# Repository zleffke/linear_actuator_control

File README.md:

# linear_actuator_control
KiCAD layout &amp; Arduino code for large linear actuator controller

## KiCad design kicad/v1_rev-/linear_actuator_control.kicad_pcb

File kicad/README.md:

# linear_actuator_control
KiCAD layout for linear actuator controller

### Directories:

v1_rev- : Initial KiCAD design

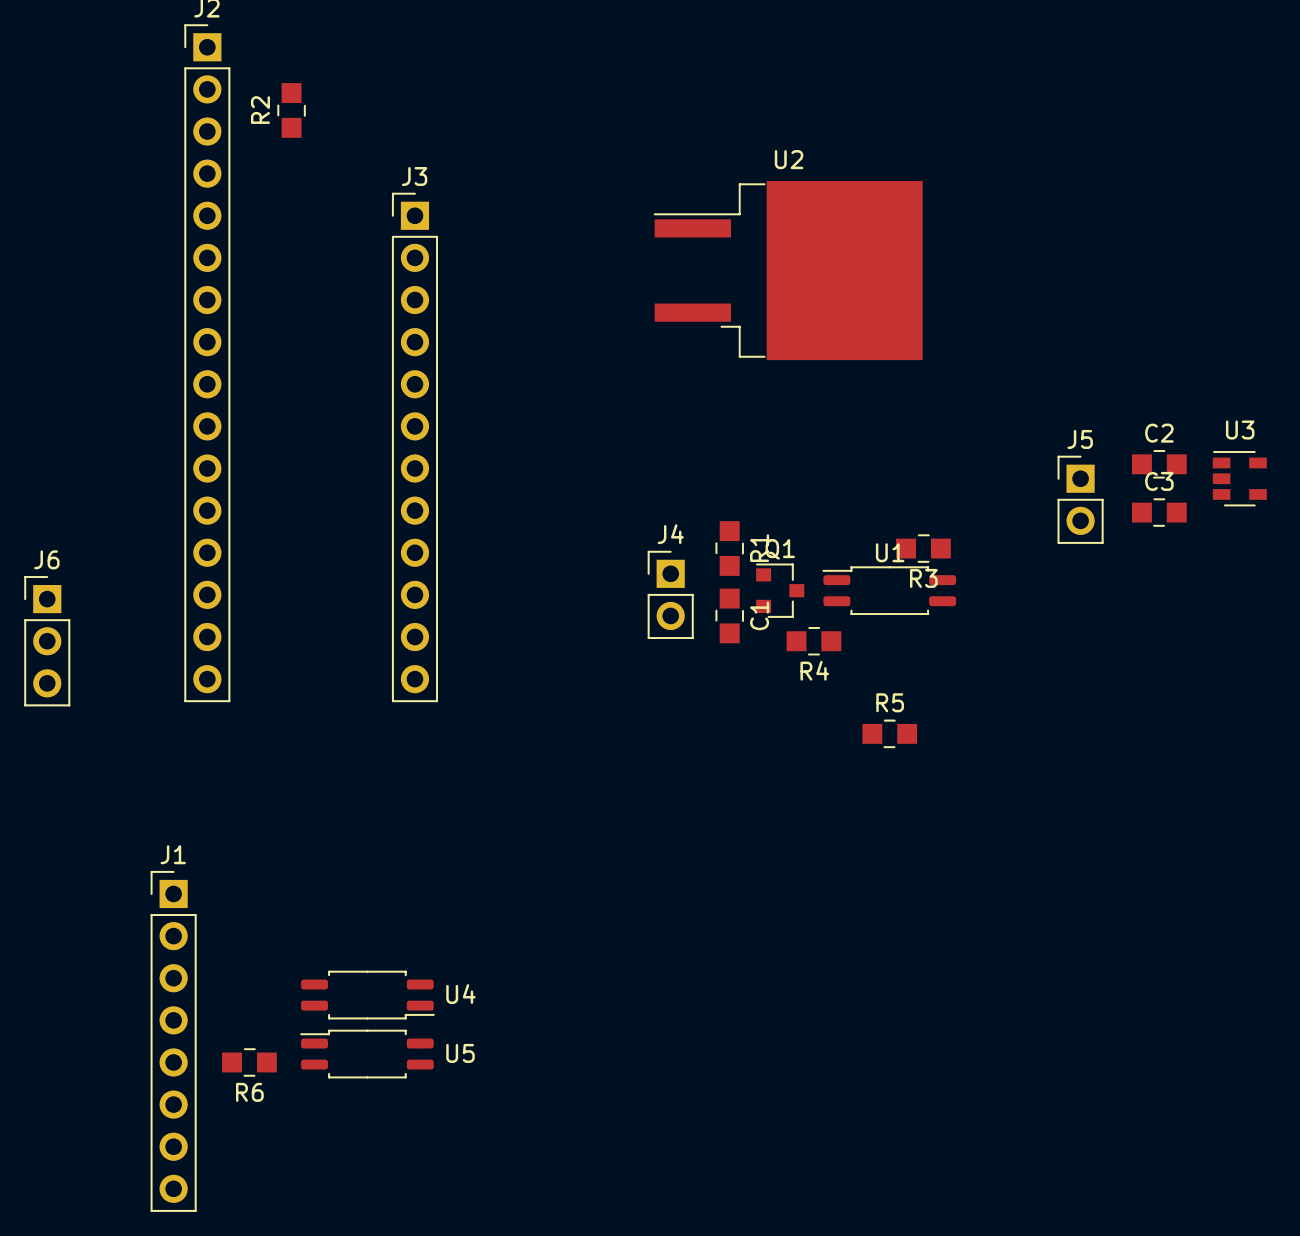
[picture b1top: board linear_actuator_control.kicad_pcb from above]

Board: 2 copper layers, 21 parts (0 on the bottom side), 18 nets, no tracks yet.

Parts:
C1, C2, C3: C; 0805
J1: G2_24v13; PinHeader_1x08_P2.54mm_Vertical
J2: feather32u4; PinHeader_1x16_P2.54mm_Vertical
J3: feather32u4; PinHeader_1x12_P2.54mm_Vertical
J4: Sensor; PinHeader_1x02_P2.54mm_Vertical
J5: Power; PinHeader_1x02_P2.54mm_Vertical
J6: LCD; PinHeader_1x03_P2.54mm_Vertical
Q1: DMG3414U; SOT-23
R1, R2, R3: 10k; 0805
R4, R5: 1k; 0805
R6: 270; 0805
U1, U4, U5: FODM217C; SOP-4_4.4x2.6mm_P1.27mm
U2: NCV8674; TO-263-2
U3: SPX3819M5-L-5-0; SOT-23-5

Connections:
0_RX: J2.14, R3.1, U1.4
1_TX: J2.15, J6.2
5_PWM: J1.3, J3.10
6: J1.2, J3.9
18_A0: J1.6, J2.5
19_A1: J2.6, R5.1
+3V3: J2.2, R2.2, R3.2, U5.1
+12V: C3.1, R1.1, U1.1, U2.3
GND: C1.2, C2.2, C3.2, J1.1, J2.4, J2.16, J4.2, J5.2, J6.3, Q1.2, U1.3, U2.2, U4.2, U4.3, U5.3
unnamed: C1.1, J4.1, Q1.1, R1.2
unnamed: C2.1, J5.1, U2.1
unnamed: Q1.3, R4.2
unnamed: R4.1, U1.2
unnamed: R5.2, U4.1
unnamed: R6.1, U5.2
SCL: J3.11, R2.1, U5.4
~FLT: J1.5, R6.2
~SLP: J1.4, U4.4

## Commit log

2020-08-22 initial commit of empty kicad project
2021-02-22 mass commit
